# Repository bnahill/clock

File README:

This is based on the MSP430 Launchpad and should support all 4 of the various devices that TI has provided with this in the past. Change the chip name in Makefile and adjust paths according to your MSPGCC configuration.

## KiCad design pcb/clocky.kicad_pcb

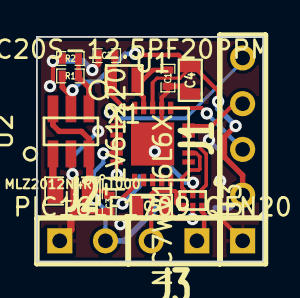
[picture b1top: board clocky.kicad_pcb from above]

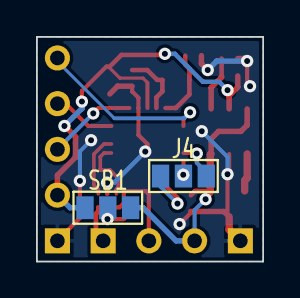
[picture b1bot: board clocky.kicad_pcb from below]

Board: 2 copper layers, 12.6 x 12.5 mm, 17 parts (2 on the bottom side), 18 nets.

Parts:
C1, C2: C; SM0402
C3: 0.1u; SM0402
C4, C5: GRM188R60J106ME47D; SM0603
J1: CONN_5; SIL-5
J2, J3: CONN_2; SIL-2
J4: CONN_3; GS3
L1: MLZ2012N4R7LT000; SM0805
R1, R2: R; SM0402
SB1: GS3
U1: PIC16LF1709_QFN20; PIC_QFN20
U2: TLV61220; TLV61220_TSOT23
U3: NC7WV16L6X; NC7WV16_MICROPAK
X1: SC20S-12.5PF20PPM; SC-20S

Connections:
/PGC: J1.4, U1.15
/PGD: J1.3, U1.16
/VBATT: C3.1, J2.2, L1.1, SB1.3, U2.3, U2.6
/~MCLR: J1.5, U1.1
GND: C1.1, C2.1, C3.2, C4.2, C5.2, J1.1, J2.1, R2.2, U1.17, U1.PAD, U2.2, U3.GND
unnamed: C1.2, U1.19, X1.2
unnamed: J3.2, U3.Y2
unnamed: C2.2, U1.20, X1.1
unnamed: L1.2, U2.1
unnamed: U1.12, U3.A2
unnamed: J3.1, U3.Y1
unnamed: C5.1, SB1.2, U3.VDD
unnamed: J4.1, U1.6
unnamed: J4.2, U1.5
unnamed: J4.3, U1.4
unnamed: R1.2, R2.1, U2.4
unnamed: U1.13, U3.A1
VDD: C4.1, J1.2, R1.1, SB1.1, U1.18, U2.5

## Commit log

2012-02-26 Builds for lower-end controller but with no RNG
2012-02-26 Use WDT instead of second timer to support wussy devices for random number generation
2012-03-07 Works correctly at 8 ticks/sec
2012-03-12 Added README and changed duty cycle again because I think some ticks are being skipped
2015-02-10 Added schematic and partial libraries for tiny board design
2015-02-11 Added crystal, fixed footprints, started PCB at 1.4x1.2cm
2015-02-12 Added some extra pads to expose more micro pins, selectable power supply
2015-02-12 Added gerbers for rev1a
